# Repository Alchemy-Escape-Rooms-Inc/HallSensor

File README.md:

# Hall Sensor
Repository dedicated to Alchemy Escape Rooms digital hall sensor

# Folder Structure
## Assembly
Documentation on building

## BOM
.xlsx bom for all parts

## Design
Source code, source models, pcb projects, etc.

## Documentation
User and integration guides, etc.

## Exports
Compiled binaries, printable stl models, etc.

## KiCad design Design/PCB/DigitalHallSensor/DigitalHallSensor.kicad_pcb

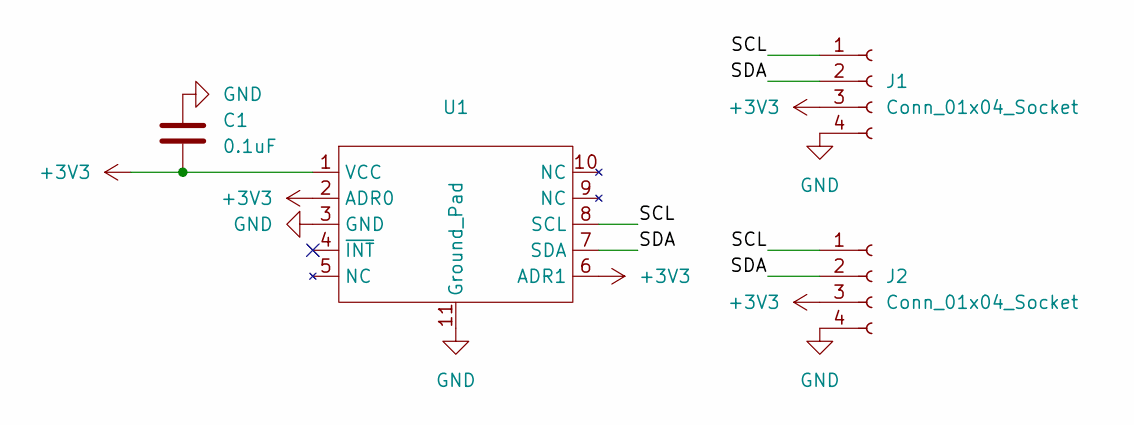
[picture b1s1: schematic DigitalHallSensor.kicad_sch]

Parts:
C1: 0.1uF; C_0402_1005Metric_Pad0.74x0.62mm_HandSolder
J1, J2: Conn_01x04_Socket; JST_PH_B4B-PH-K_1x04_P2.00mm_Vertical
U1: DFN-10-EJ

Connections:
+3V3: C1.2, J1.3, J2.3, U1.1 (VCC), U1.2 (ADR0), U1.6 (ADR1)
/SCL: J1.1, J2.1, U1.8 (SCL)
/SDA: J1.2, J2.2, U1.7 (SDA)
GND: C1.1, J1.4, J2.4, U1.3 (GND), U1.11 (Ground_Pad)

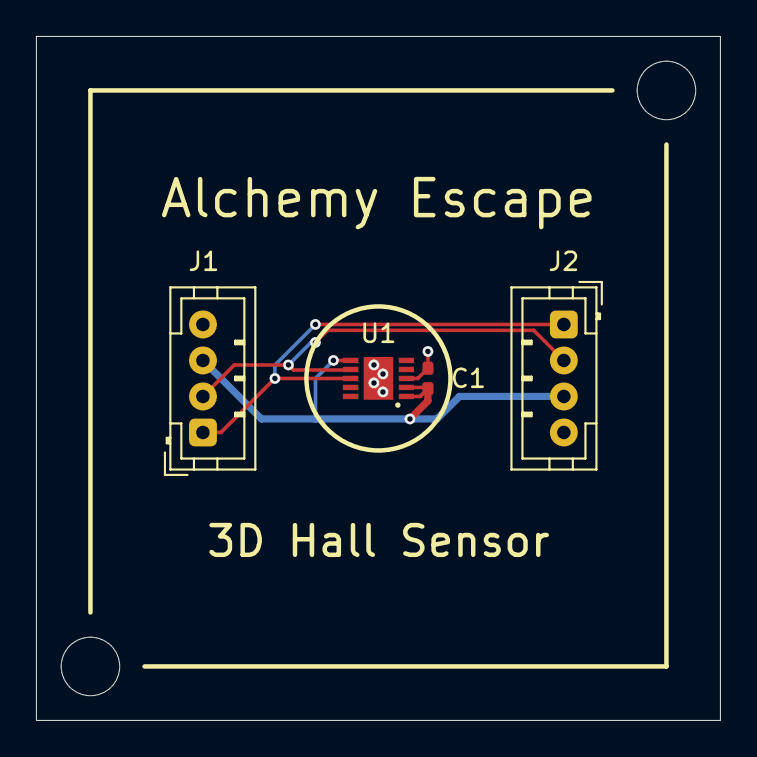
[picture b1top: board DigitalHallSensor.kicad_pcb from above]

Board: 2 copper layers, 38.0 x 38.0 mm, 4 parts (0 on the bottom side), 4 nets.

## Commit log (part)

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2024-12-20 ESP32-S3 project containing integrated hall sensor library
2024-12-28 enabled i2c scanner, expanded reference to handle multiple sensors, made pin initialization function public
2024-12-28 Supporting documentation and PCB project
2024-12-28 Added firmware exports
2024-12-28 Added hall sensor wiring document
2024-12-28 Brought pins.h and pins.cpp inline with esp ide reference
2025-10-10 Add files via upload
    Added two one click easy to use arduino ide programs to scan and rewrite the hall sensor ids
